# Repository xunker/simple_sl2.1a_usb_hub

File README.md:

# "SLuper SLimple" SL2.1A USB 2.0 Hub

A 4-port USB 2.0 hub on a 1-inch (25.4mm) square board. Utilizes the
(hand-solderable) SL2.1A USB Hub Controller with footprint for an optional
crystal oscillator. Features length-matched data lines for maximum
potato-performance.

Uses only surface-mount components and, except for the IC and (optional)
crystal, all of them can be found in your parts bin or scavenged from other
equipment.

The PCB can be hand-etched on a single-sized PCB, as long as jumper wires are
added to connect all the 5V pins for the USB connections.

## Bill of Materials

* The PCB itself
* **U1**: SL2.1A, SOIC-16 package
* **Y1**: 12Mhz crystal Oscillator, 3225 4-pin package
  - optional but recommended
* **C1**, **C2**: 10uF ceramic capacitor, 1206 package
  * quantity: 2
  * should be rated for 6V or higher
* **C9**, **C10**, **C11**, **C12**: 100uF ceramic capacitor, 1206 package
  * quantity 4
  * should be rated for 10V or higher
  * C11/C12 can share a common capacitor attached between the
    pads if you only have 3 on hand
* **USB0**, **USB1**, **USB2**, **USB3**, **USB4**: 2.54mm 1x4 breakaway headers
  * quantity: 5
  * optional, you can solder USB connections directly to the pads if you wish

### Sourcing USB Connectors

This BoM does not include the actual USB upstream and downstream connectors
themselves.

In my case, I used a handful of USB connector breakouts (search for
"usb-a breakout" on your marketplace of choice) for the downstream connectors,
and cut up an old USB cable for the upstream (USB0) connector.

You could also cut up a few USB-A-F to USB-A-M extensions instead and solder the
ends directly to the pads if you want them to be permanent.

## Hand-Solder Construction Order

Because space on this board is limited, it is recommended to solder the
components in this order if you are soldering by hand using an iron.

1. Y1 (optional, but will be hard to solder after capacitors are in place)
    * If you choose to skip the external crystal, you must connect pin 1 of Y1
      to GND
    * Pin 1 is the pad closest to the silkscreened "Y1"
2. U1
3. C1
4. C2
5. C3
6. C9
7. ..remaining components in any order

## SL2.1A Information

A [translated datasheet](./corechips-sl2-1a_usb_hub_controller_datasheet_translated.pdf) is provided in this repo.

If your hub is functioning correctly, this is the USB information you should be
able to see when connected:

```
Reporting name: USB2.0 HUB
Product ID:     0x0101
Vendor ID:      0x1a40  (TERMINUS TECHNOLOGY INC.)
Version:        1.00
Speed:          Up to 480 Mb/s

Current Available (mA):       500
Current Required (mA):        100
Extra Operating Current (mA):	0
```

Information may vary depending in the version of the IC you have.

# Changelog

### Initial Revision - Sept 2024

First working version from fab.

# Repository

The canonical repository is https://github.com/xunker/simple_sl2.1a_usb_hub

For the license, see [LICENSE](./LICENSE).

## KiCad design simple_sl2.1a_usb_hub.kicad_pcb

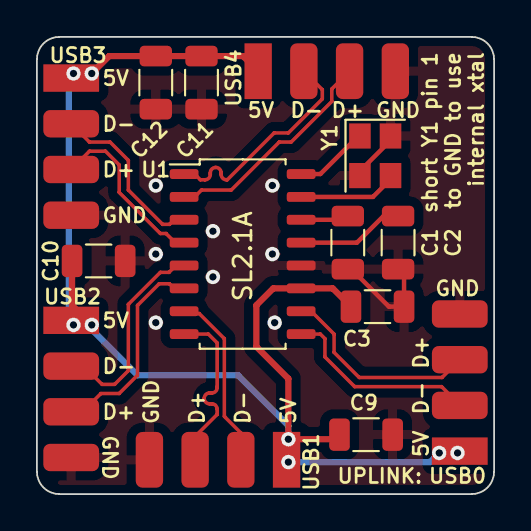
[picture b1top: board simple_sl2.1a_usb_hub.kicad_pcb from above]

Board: 2 copper layers, 25.4 x 25.4 mm, 14 parts (0 on the bottom side), 16 nets.

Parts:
C1, C2, C3: 10uF; C_1206_3216Metric
C9, C10, C11, C12: 100uF/16V; C_1206_3216Metric
U1: SL2.1A; SOIC-16_4.55x10.3mm_P1.27mm
USB0, USB1, USB2, USB3, USB4: Conn_01x04_Male; 2.54mm 1x4 header edge - no silks
Y1: Crystal_GND24; Crystal_SMD_3225-4Pin_3.2x2.5mm

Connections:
D1+: U1.8 (DP1), USB1.3
D1-: U1.7 (DM1), USB1.2
D2+: U1.6 (DP2), USB2.3
D2-: U1.5 (DM2), USB2.2
D3+: U1.4 (DP3), USB3.3
D3-: U1.3 (DM3), USB3.2
D4+: U1.2 (DP4), USB4.3
D4-: U1.1 (DM4), USB4.2
DU+: U1.10 (UDP), USB0.3
DU-: U1.9 (UDM), USB0.2
Earth: C1.2, C2.2, C3.2, C9.2, C10.2, C11.2, C12.2, U1.12 (GND), USB0.4, USB1.4, USB2.4, USB3.4, USB4.4, Y1.2, Y1.4
unnamed: C1.1, U1.14 (VDD18)
unnamed: C2.1, U1.13 (VDD3)
unnamed: U1.15 (XOUT), Y1.3
unnamed: U1.16 (XIN), Y1.1
VBUS: C3.1, C9.1, C10.1, C11.1, C12.1, U1.11 (VCC5V), USB0.1, USB1.1, USB2.1, USB3.1, USB4.1

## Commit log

2024-10-18 Initial kicad commit after fab
2024-10-18 renamed so it can be linked
2024-10-18 Add images, more detail
2024-10-18 added schematic
2024-10-18 Added more pictures
